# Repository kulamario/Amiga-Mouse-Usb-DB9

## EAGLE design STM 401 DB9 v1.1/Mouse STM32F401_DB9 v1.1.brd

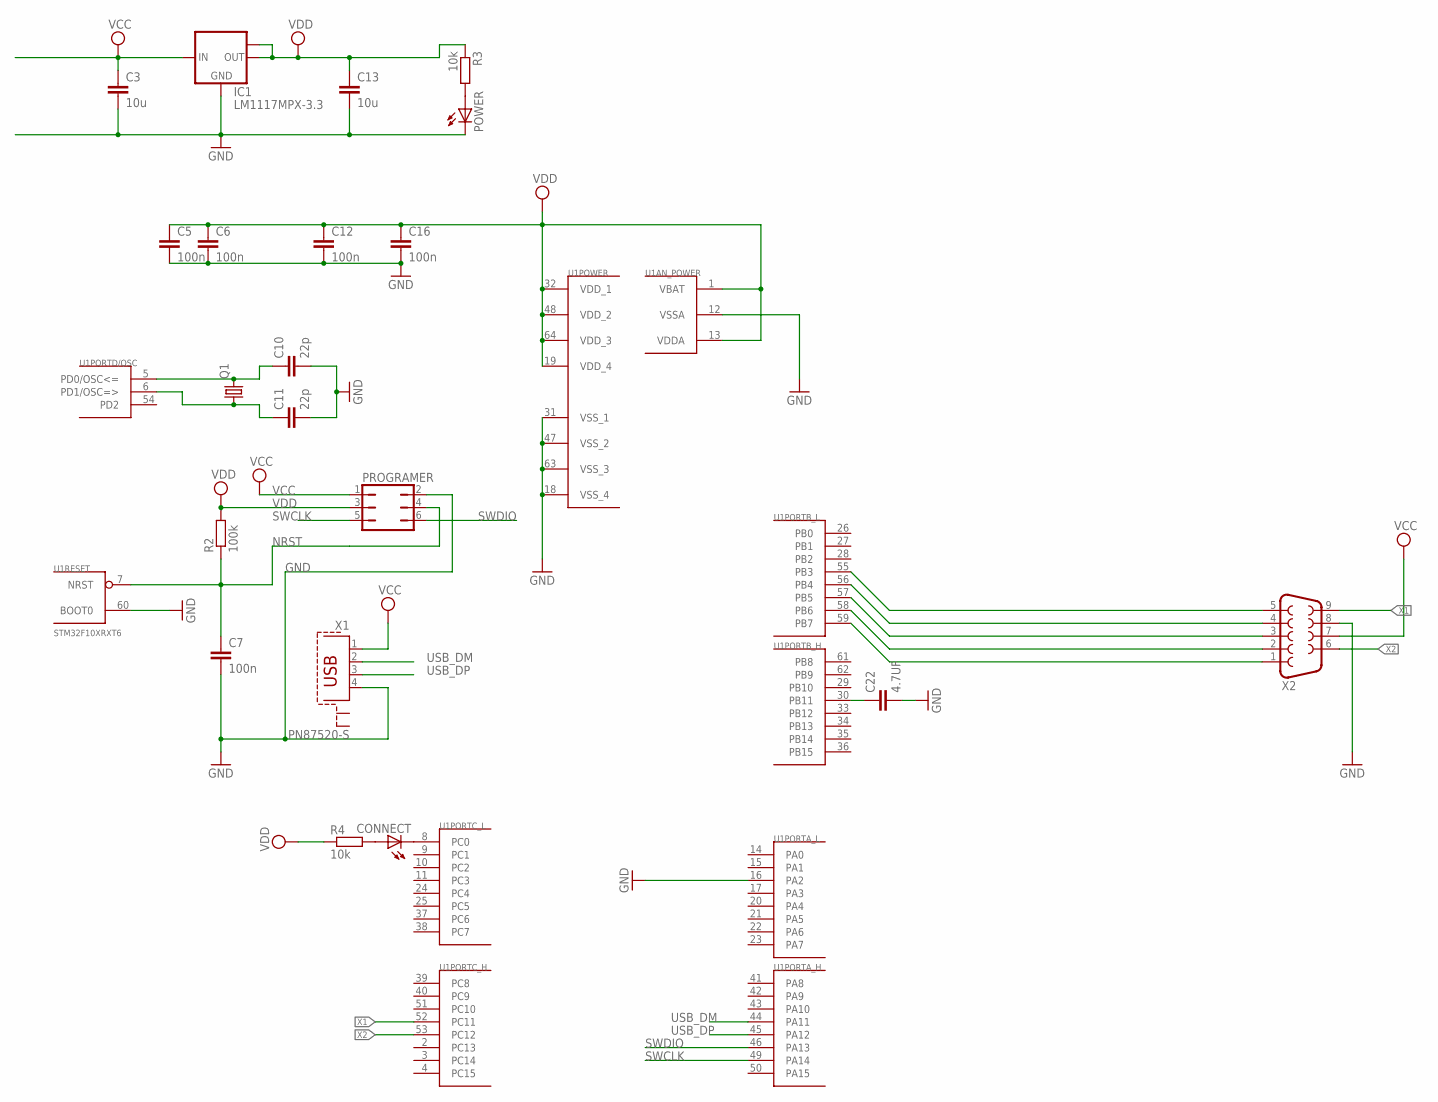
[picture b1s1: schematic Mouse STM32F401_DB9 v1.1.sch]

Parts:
C3, C13: 10u; C1206
C5, C6, C7, C12, C16: 100n; C0603
C10, C11: 22p; C0603
C22: 4.7UF; C1206
CONNECT: LEDSML0805; SML0805
IC1: LM1117MPX-3.3; SOT223
POWER: LEDSML0805; SML0805
PROGRAMER: JP3Q
Q1: CRYSTALHC49S; HC49/S
R2: 100k; R0603
R3, R4: 10k; R0603
U1: STM32F10XRXT6; TQFP64
X1: PN87520-S
X2: F09HP

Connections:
GND: C3.2, C5.2, C6.2, C7.2, C10.2, C11.2, C12.2, C13.2, C16.2, C22.2, IC1.1 (GND), POWER.C, PROGRAMER.2, U1.12 (VSSA), U1.16 (PA2), U1.18 (VSS_4), U1.31 (VSS_1), U1.47 (VSS_2), U1.60 (BOOT0), U1.63 (VSS_3), X1.4, X2.8
unnamed: C10.1, Q1.2, U1.5 (PD0/OSC<=)
unnamed: C11.1, Q1.1, U1.6 (PD1/OSC=>)
unnamed: CONNECT.C, U1.8 (PC0)
unnamed: C22.1, U1.30 (PB11)
unnamed: U1.55 (PB3), X2.5
unnamed: CONNECT.A, R4.2
unnamed: U1.56 (PB4), X2.4
unnamed: U1.58 (PB6), X2.2
unnamed: POWER.A, R3.2
unnamed: U1.59 (PB7), X2.1
unnamed: U1.57 (PB5), X2.3
NRST: C7.1, PROGRAMER.4, R2.1, U1.7 (NRST)
SWCLK: PROGRAMER.5, U1.49 (PA14)
SWDIO: PROGRAMER.6, U1.46 (PA13)
USB_DM: U1.44 (PA11), X1.2
USB_DP: U1.45 (PA12), X1.3
VCC: C3.1, IC1.3 (IN), PROGRAMER.1, X1.1, X2.7
VDD: C5.1, C6.1, C12.1, C13.1, C16.1, IC1.2 (OUT), IC1.TAB (OUT1), PROGRAMER.3, R2.2, R3.1, R4.1, U1.1 (VBAT), U1.13 (VDDA), U1.19 (VDD_4), U1.32 (VDD_1), U1.48 (VDD_2), U1.64 (VDD_3)
X1: U1.52 (PC11), X2.9
X2: U1.53 (PC12), X2.6

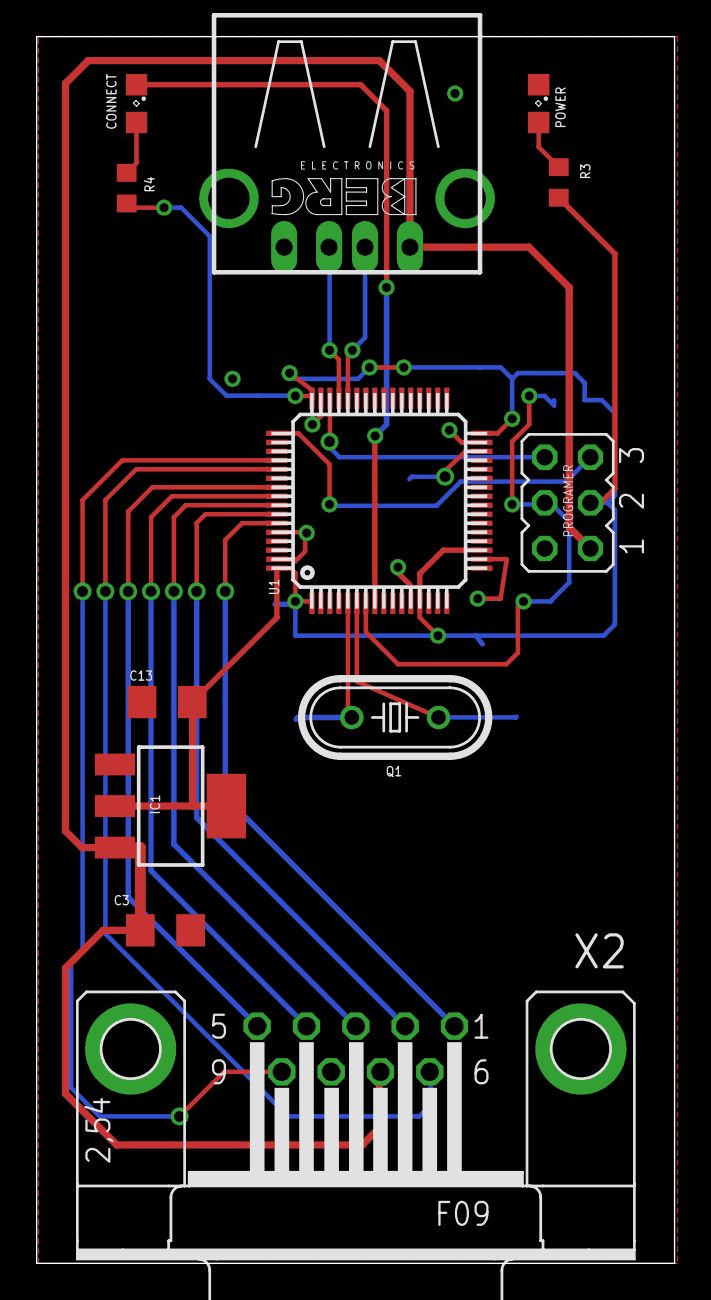
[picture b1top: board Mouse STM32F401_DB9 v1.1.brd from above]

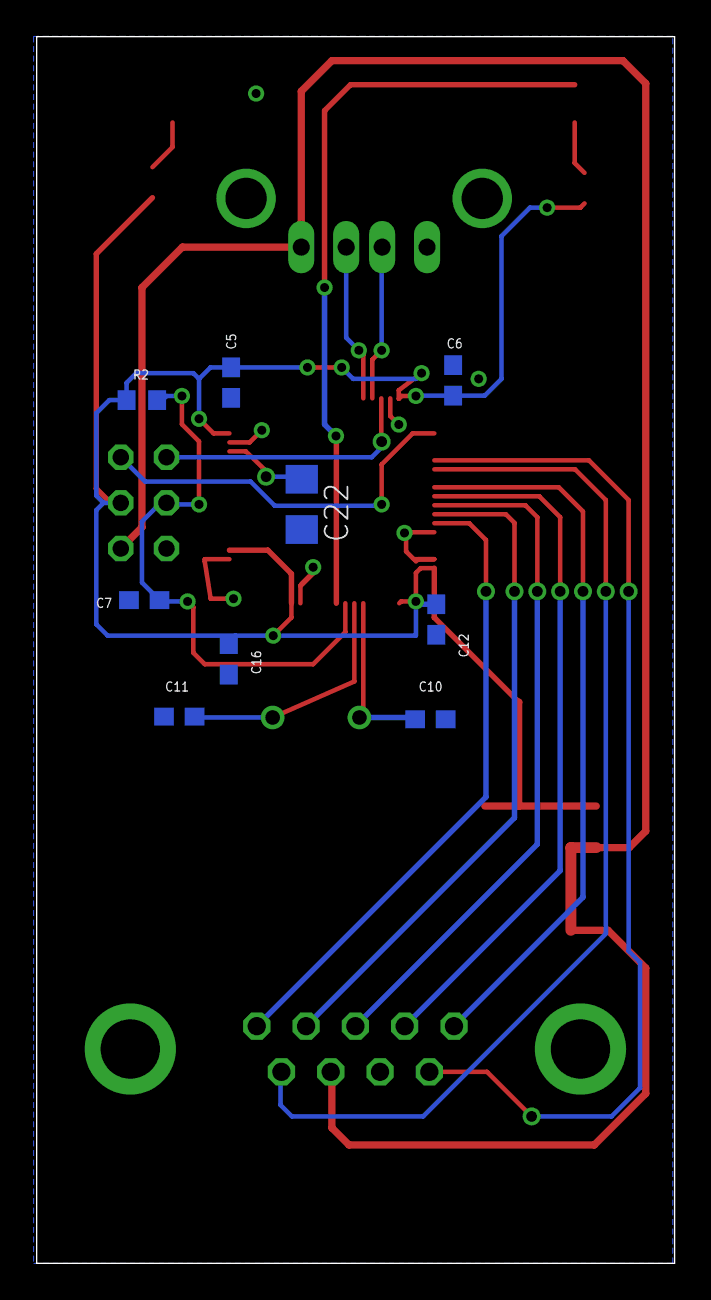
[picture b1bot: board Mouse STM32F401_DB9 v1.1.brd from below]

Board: 2 copper layers, 35.5 x 68.2 mm, 21 parts (9 on the bottom side), 21 nets.

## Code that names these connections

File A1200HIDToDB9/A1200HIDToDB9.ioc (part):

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Mcu.Name=STM32F401R(B-C)Tx
Mcu.Package=LQFP64
Mcu.UserName=STM32F401RBTx
PA11.Mode=Host_Only
PA11.Signal=USB_OTG_FS_DM
PA12.Mode=Host_Only
PA12.Signal=USB_OTG_FS_DP
PB3.GPIOParameters=PinState,GPIO_Label
PB3.GPIO_Label=MB
PB3.PinState=GPIO_PIN_SET
PB3.Signal=GPIO_Output
PB4.GPIOParameters=PinState,GPIO_Label
PB4.GPIO_Label=RHQ
PB4.PinState=GPIO_PIN_SET
PB4.Signal=GPIO_Output
PB5.GPIOParameters=PinState,GPIO_Label
PB5.GPIO_Label=LVQ
PB5.PinState=GPIO_PIN_SET
PB5.Signal=GPIO_Output
PB6.GPIOParameters=PinState,GPIO_Label
PB6.GPIO_Label=BH
PB6.PinState=GPIO_PIN_SET
PB6.Signal=GPIO_Output
PB7.GPIOParameters=PinState,GPIO_Label
PB7.GPIO_Label=FV
PB7.PinState=GPIO_PIN_SET
PB7.Signal=GPIO_Output
PC0.GPIOParameters=PinState,GPIO_Label
PC0.GPIO_Label=LED
PC0.PinState=GPIO_PIN_SET
PC0.Signal=GPIO_Output
PC11.GPIOParameters=PinState,GPIO_Label
PC11.GPIO_Label=RB
PC11.PinState=GPIO_PIN_SET
PC11.Signal=GPIO_Output
PC12.GPIOParameters=PinState,GPIO_Label
PC12.GPIO_Label=LB
PC12.PinState=GPIO_PIN_SET
PC12.Signal=GPIO_Output
PH0\ -\ OSC_IN.Mode=HSE-External-Oscillator
PH0\ -\ OSC_IN.Signal=RCC_OSC_IN
PH1\ -\ OSC_OUT.Mode=HSE-External-Oscillator
PH1\ -\ OSC_OUT.Signal=RCC_OSC_OUT
RCC.HSE_Timout=1000
RCC.HSE_VALUE=8000000
RCC.SYSCLKFreq_VALUE=84000000
RCC.SYSCLKSource=RCC_SYSCLKSOURCE_PLLCLK
board=custom

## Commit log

2022-12-11 Initial firmware - source code and build debug and release
2022-12-13 LED on/off fix
2023-02-14 Project upgrade and IWDG 500ms
